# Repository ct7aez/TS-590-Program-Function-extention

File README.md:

# TS-590-Program-Function-extention
TS-590s(G) Program Funcion (PF Keys) extention circuit and pcb as in TS-590 IDM.
This is a small project for implementing the TS-590 IDM manual ideia.

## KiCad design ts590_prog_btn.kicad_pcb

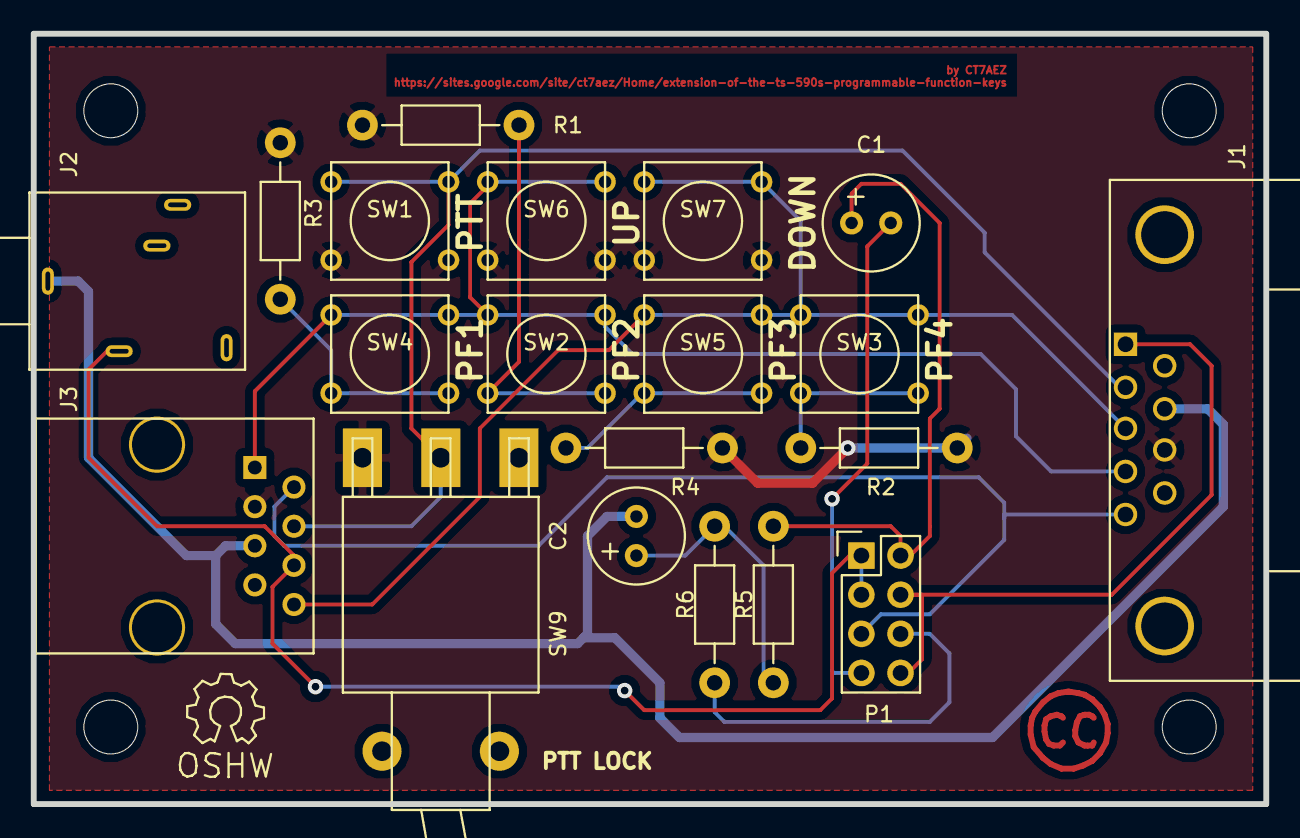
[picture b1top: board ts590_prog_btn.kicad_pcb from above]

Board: 2 copper layers, 80.0 x 50.0 mm, 20 parts (0 on the bottom side), 16 nets.

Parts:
C1: 1u; Elko_vert_11.2x6.3mm_RM2.5
C2: 10u; Elko_vert_11.2x6.3mm_RM2.5
J1: DB9; DB9FC
J2: JACK_TRS_6PINS; myaudiojack
J3: RJ45; RJ45_8
P1: CONN_02X04; Pin_Header_Straight_2x04
R1, R2: 100K; Resistor_Horizontal_RM10mm
R3, R4: 22K; Resistor_Horizontal_RM10mm
R5: 15K; Resistor_Horizontal_RM10mm
R6: 1K; Resistor_Horizontal_RM10mm
SW1: PTT; SW_PUSH_SMALL
SW2: PF2; SW_PUSH_SMALL
SW3: PF4; SW_PUSH_SMALL
SW4: PF1; SW_PUSH_SMALL
SW5: PF3; SW_PUSH_SMALL
SW6: UP; SW_PUSH_SMALL
SW7: DOWN; SW_PUSH_SMALL
SW9: PTT_LOCK; SW_SPDT

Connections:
/EXTMIC: J2.2, J3.6, P1.1, P1.3
/MICCN1_MIC: J1.1, P1.4, P1.8
/MICCN2_PTT: J1.2, J3.4, SW1.1, SW9.2
/MICCN3_DOWN: J1.3, J3.8, SW3.1, SW5.1, SW7.1
/MICCN4_UP: J1.4, J3.1, SW2.1, SW4.1, SW6.1
/MICCN5_8V: J1.5, J3.2, P1.5
/MICCN5_8V_PWRSW: P1.6, R6.1
/MIC_ELECT: C1.1, P1.2, R5.2
GND: J1.8, J3.3, R1.2, R2.2, R3.2, R4.2, SW1.2, SW6.2, SW7.2, SW9.3
GNDA: C2.2, J1.7, J2.1, J3.5
unnamed: C1.2, P1.7
unnamed: C2.1, R5.1, R6.2
unnamed: R1.1, SW2.2
unnamed: R2.1, SW3.2
unnamed: R3.1, SW4.2
unnamed: R4.1, SW5.2

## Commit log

2015-04-17 project started
2015-04-17 Create README.md
    started
2015-04-17 add pcb
2015-04-21 small change in readme just to clarify
2015-04-23 added the first pcb draw
2015-04-26 add jack on pcb and new layout
2015-04-27 Corrected the mic pwr selection on pcb and sch.
2015-04-27 small changes on pcb
2015-04-27 added BOM and some pcb tweaks
2015-07-14 Corrected DB-9 position on PCB
2015-07-14 gitignore tweak
2015-07-14 ignore update

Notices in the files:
ts590_prog_btn.kicad_pcb:
visite http://creativecommons.org/licenses/by/4.0/.
Este trabalho está licenciado sob uma Licença Creative Commons
